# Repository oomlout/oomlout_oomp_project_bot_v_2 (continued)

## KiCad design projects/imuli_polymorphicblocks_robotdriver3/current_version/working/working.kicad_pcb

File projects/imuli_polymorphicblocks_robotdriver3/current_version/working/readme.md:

# polymorphicblocks
 
## summary 
* id: imuli_polymorphicblocks_robotdriver3
* user: imuli
* name: polymorphicblocks
* board: robotdriver3
* repo: https://github.com/imuli/PolymorphicBlocks
* src_file_repo_kicad_pcb: examples/RobotDriver3/RobotDriver3.kicad_pcb
* src_file_repo_kicad_pcb_link: https://github.com/imuli/PolymorphicBlocks/tree/master/examples/RobotDriver3/RobotDriver3.kicad_pcb

* src_file_repo_sch: 
* src_file_repo_sch_link: https://github.com/imuli/PolymorphicBlocks/tree/master/
* full details link: https://github.com/oomlout/oomlout_oomp_project_bot_v_2/tree/main/projects/imuli_polymorphicblocks_robotdriver3/current_version/working

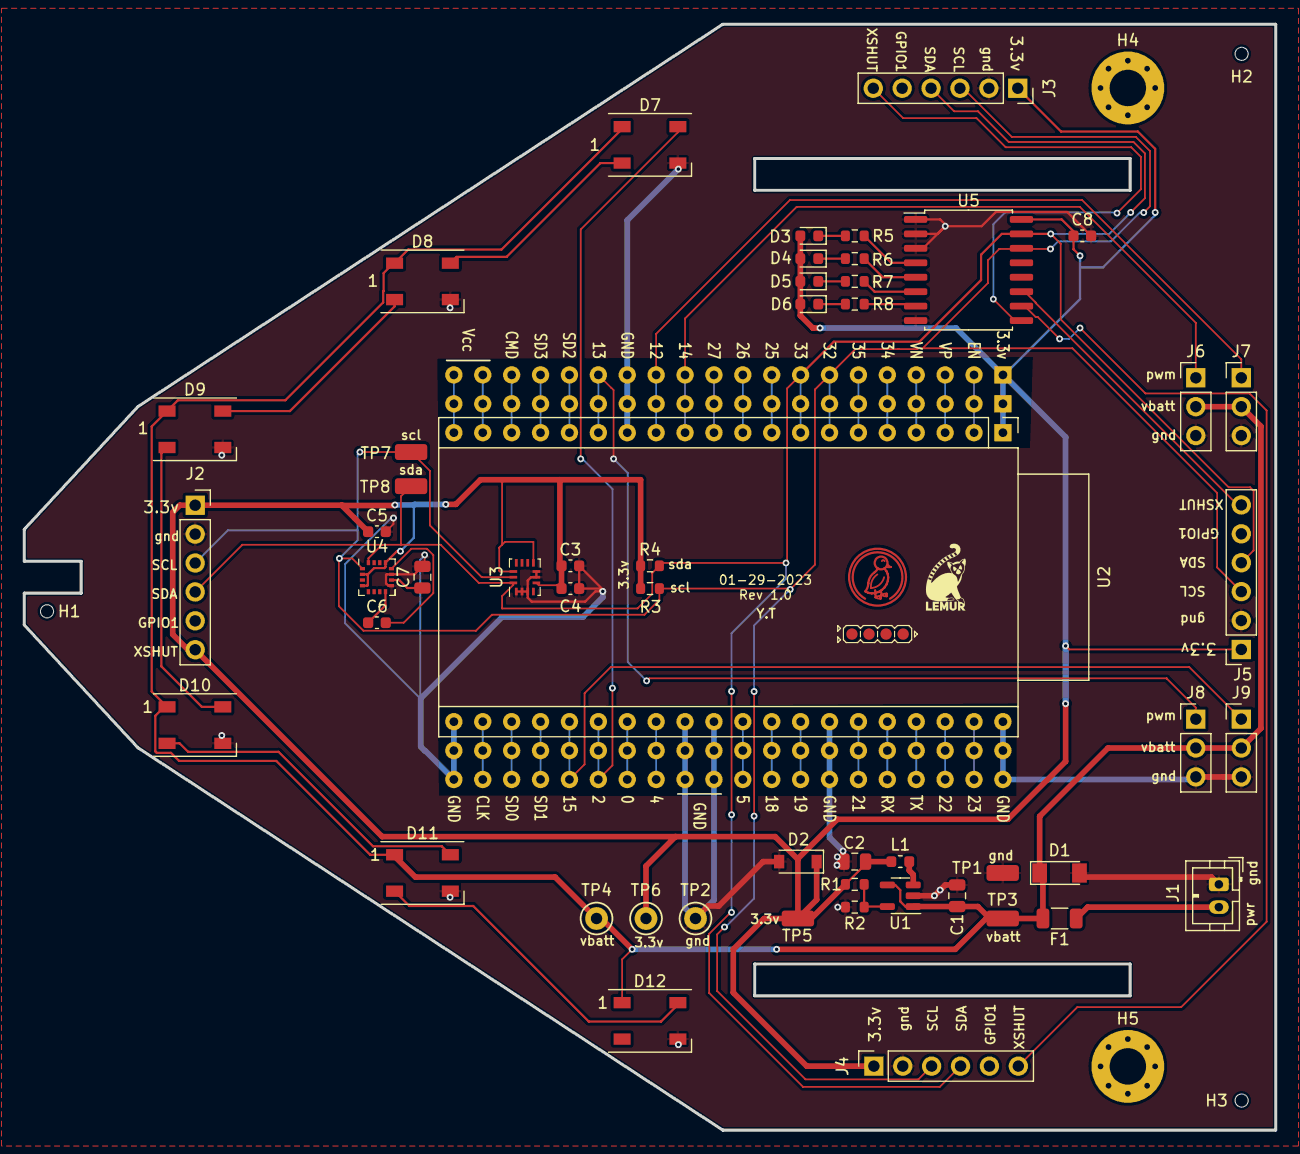
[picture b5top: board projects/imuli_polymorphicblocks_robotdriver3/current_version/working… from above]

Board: 2 copper layers, 110.0 x 97.2 mm, 60 parts (0 on the bottom side), 32 nets.

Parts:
C1, C2, C7: C_0805_2012Metric
C3, C4, C5, C6, C8: C_0603_1608Metric
D1: ZMM5V6-M (ST(Semtech)) - 100nA@1V 25? Single 5.2V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; D_MiniMELF
D2: BZT52C3V6 (SMC(Sangdest Microelectronicstronic (N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; D_SOD-123
D3, D4, D5, D6: KT-0603R (Hubei KENTO Elec) - Red 615~630nm 1.9~2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; LED_0603_1608Metric
D7, D8, D9, D10, D11, D12: WS2812B (Worldsemi); LED_WS2812B_PLCC4_5.0x5.0mm_P3.2mm
F1: MF-NSMF200-2 (BOURNS) - 6V 2A 100A 4A 1206 Resett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; R_1206_3216Metric
H1, H2, H3: JlcToolingHole_1.152mm
H4, H5: M3; MountingHole_3.2mm_M3_Pad_Via
J1: B2B-PH-K (JST); JST_PH_B2B-PH-K_1x02_P2.00mm_Vertical
J2, J3, J4, J5: PinSocket2.54 1x6 (Generic); PinSocket_1x06_P2.54mm_Vertical
J6, J7, J8, J9: PinHeader2.54 1x3 (Generic); PinHeader_1x03_P2.54mm_Vertical
L1: L_0603_1608Metric
R1, R2, R3, R4, R5, R6, R7, R8: R_0603_1608Metric
TP1: 5015 (Keystone) - gnd; TestPoint_TE_RCT_0805
TP2: 5001 (Keystone) - gnd; TestPoint_Keystone_5000-5004_Miniature
TP3: 5015 (Keystone) - vbatt; TestPoint_TE_RCT_0805
TP4: 5001 (Keystone) - vbatt; TestPoint_Keystone_5000-5004_Miniature
TP5: 5015 (Keystone) - v3v3; TestPoint_TE_RCT_0805
TP6: 5001 (Keystone) - v3v3; TestPoint_Keystone_5000-5004_Miniature
TP7: 5015 (Keystone) - i2c_chain_0.scl; TestPoint_TE_RCT_0805
TP8: 5015 (Keystone) - i2c_tp._io_sda_link; TestPoint_TE_RCT_0805
U1: AP3418 (Diodes Incorporated); SOT-23-5
U2: ESP32-WROVER-DEV; ESP32-WROVER-DEV_Chicken
U3: LSM6DS3TR-C (STMicroelectronics); Bosch_LGA-14_3x2.5mm_P0.5mm
U4: QMC5883L (QST); LGA-16_3x3mm_P0.5mm
U5: PCF8574AT (NXP); SOIC-16W_7.5x10.3mm_P1.27mm
U6: Lemur; Symbol_LemurSmall
U7: Duck; Symbol_Duckling
U8: IdDots4; Indicator_IdDots_4

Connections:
batt.pwr: F1.1, J1.2
expander.io.led_0: R5.2, U5.4
expander.io.led_1: R6.2, U5.5
expander.io.led_2: R7.2, U5.6
expander.io.led_3: R8.2, U5.7
expander.io.tof_xshut_1: J3.6, U5.9
expander.io.tof_xshut_2: J4.6, U5.10
expander.io.tof_xshut_3: J5.6, U5.11
gnd: C1.2, C2.2, C3.2, C4.2, C5.2, C7.2, C8.2, D1.2, D2.2, D7.3, D8.3, D9.3, D10.3, D11.3, D12.3, J1.1, J2.2, J3.2, J4.2, J5.2, J6.3, J7.3, J8.3, J9.3, R2.2, TP1.1, TP2.1, U1.2, U2.14, U2.21, U2.29, U2.30, U2.34, U2.40, U3.1, U3.2, U3.3, U3.6, U3.7, U4.9, U4.11, U5.1, U5.2, U5.3, U5.8
i2c_chain_0.scl: J2.3, J3.3, J4.3, J5.3, R3.2, TP7.1, U2.7, U3.13, U4.1, U5.14
i2c_chain_0.sda: J2.4, J3.4, J4.4, J5.4, R4.2, TP8.1, U2.8, U3.14, U4.16, U5.15
leds.led[0].res.a: D3.1, R5.1
leds.led[1].res.a: D4.1, R6.1
leds.led[2].res.a: D5.1, R7.1
leds.led[3].res.a: D6.1, R8.1
mag.c1.pos: C7.1, U4.10
mag.set_cap.neg: C6.2, U4.12
mag.set_cap.pos: C6.1, U4.8
mcu.io2: D7.4, U2.26
reg_3v3.fb.output: R1.2, R2.1, U1.5
reg_3v3.power_path.switch: L1.1, U1.3
servo[0].pwm: J6.1, U2.12
servo[1].pwm: J7.1, U2.13
servo[2].pwm: J8.1, U2.15
servo[3].pwm: J9.1, U2.25
v3v3: C2.1, C3.1, C4.1, C5.1, C8.1, D2.1, D3.2, D4.2, D5.2, D6.2, J2.1, J2.6, J3.1, J4.1, J5.1, L1.2, R1.1, R3.1, R4.1, TP5.1, TP6.1, U2.1, U3.5, U3.8, U3.12, U4.2, U4.4, U4.13, U5.16
vbatt: C1.1, D1.1, D7.1, D8.1, D9.1, D10.1, D11.1, D12.1, F1.2, J6.2, J7.2, J8.2, J9.2, TP3.1, TP4.1, U1.1, U1.4
ws2812bArray.led[0].dout: D7.2, D8.4
ws2812bArray.led[1].dout: D8.2, D9.4
ws2812bArray.led[2].dout: D9.2, D10.4
ws2812bArray.led[3].dout: D10.2, D11.4
ws2812bArray.led[4].dout: D11.2, D12.4

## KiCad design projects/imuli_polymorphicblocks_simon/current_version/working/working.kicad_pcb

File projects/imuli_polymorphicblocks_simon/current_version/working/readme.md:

# polymorphicblocks
 
## summary 
* id: imuli_polymorphicblocks_simon
* user: imuli
* name: polymorphicblocks
* board: simon
* repo: https://github.com/imuli/PolymorphicBlocks
* src_file_repo_kicad_pcb: examples/Simon/Simon.kicad_pcb
* src_file_repo_kicad_pcb_link: https://github.com/imuli/PolymorphicBlocks/tree/master/examples/Simon/Simon.kicad_pcb

* src_file_repo_sch: 
* src_file_repo_sch_link: https://github.com/imuli/PolymorphicBlocks/tree/master/
* full details link: https://github.com/oomlout/oomlout_oomp_project_bot_v_2/tree/main/projects/imuli_polymorphicblocks_simon/current_version/working

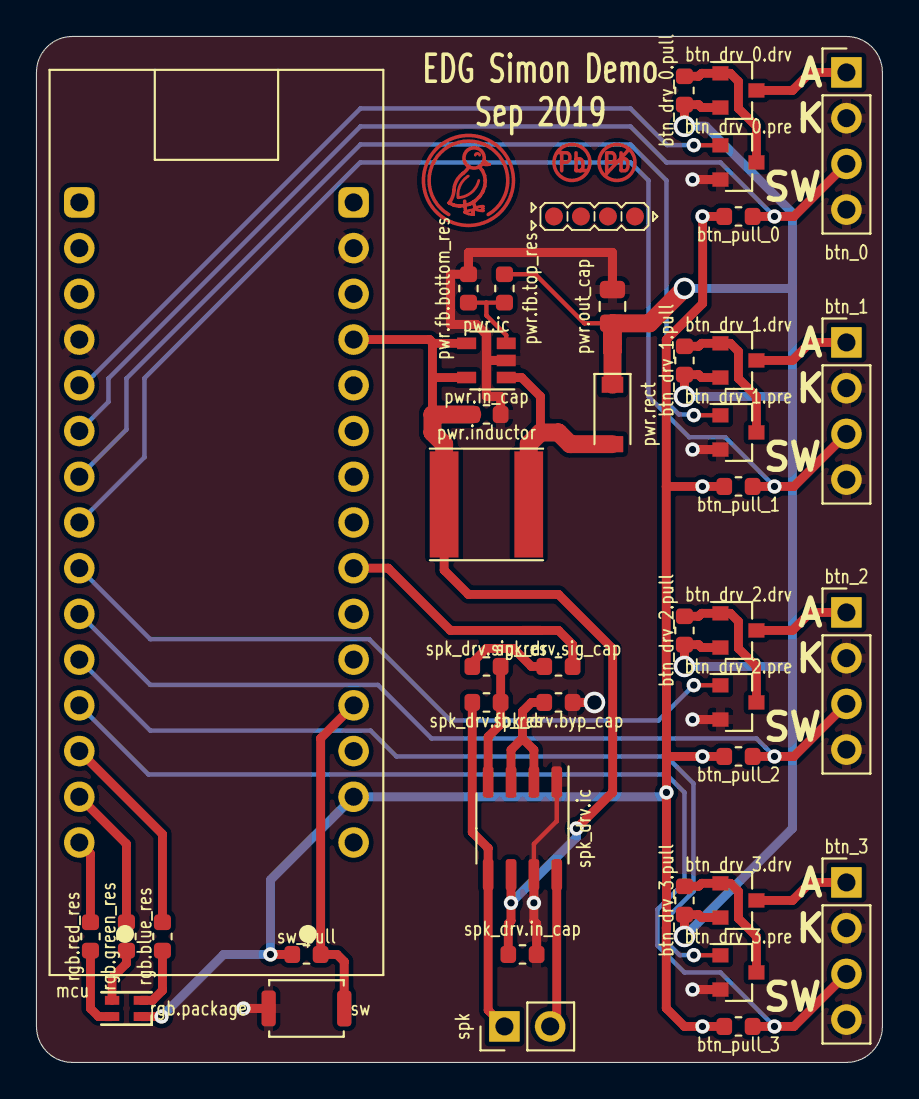
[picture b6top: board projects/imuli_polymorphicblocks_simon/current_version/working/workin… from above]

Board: 2 copper layers, 47.0 x 57.0 mm, 44 parts (0 on the bottom side), 35 nets.

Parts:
btn_0, btn_1, btn_2, btn_3: DomeButton; PinHeader_1x04_P2.54mm_Vertical
btn_drv_0.drv, btn_drv_1.drv, btn_drv_2.drv, btn_drv_3.drv: DMP3099L-7; SOT-23
btn_drv_0.pre, btn_drv_1.pre, btn_drv_2.pre, btn_drv_3.pre: NX138AKR; SOT-23
btn_drv_0.pull, btn_drv_1.pull, btn_drv_2.pull, btn_drv_3.pull: 10000, 1%, 0.1W; R_0603_1608Metric
btn_pull_0, btn_pull_1, btn_pull_2, btn_pull_3: 10000, 1%, 0.1W; R_0603_1608Metric
duck: Duck; Symbol_Duckling
id: IdDots4; Indicator_IdDots_4
leadfree: LeadFree; Indicator_LeadFree
mcu: Nucleo-F303K8; Nucleo32
pwr.fb.bottom_res: 3900, 1%, 0.1W; R_0603_1608Metric
pwr.fb.top_res: 33000, 1%, 0.1W; R_0603_1608Metric
pwr.ic: AP3012; SOT-23-5
pwr.in_cap: 1µF, 10V, CL10A105KP8NNNC; C_0603_1608Metric
pwr.inductor: 68µH, 770mA, NR6028T680M; L_Taiyo-Yuden_NR-60xx
pwr.out_cap: 10µF, 16V, CL21A106KOQNNNG; C_0805_2012Metric
pwr.rect: BAT54GWJ; D_SOD-123
rgb.blue_res, rgb.green_res, rgb.red_res: 1000, 1%, 0.1W; R_0603_1608Metric
rgb.package: LED_RGB_0606
spk: Speaker SP-1504; PinHeader_1x02_P2.54mm_Vertical
spk_drv.byp_cap, spk_drv.in_cap: 1µF, 10V, CL10A105KP8NNNC; C_0603_1608Metric
spk_drv.fb_res, spk_drv.sig_res: 22000, 1%, 0.1W; R_0603_1608Metric
spk_drv.ic: LM4871MX; SO-8_3.9x4.9mm_P1.27mm
spk_drv.sig_cap: 0.47µF, 25V, CL10B474KA8NFNC; C_0603_1608Metric
sw: switch; SW_Push_SPST_NO_Alps_SKRK
sw_pull: 10000, 1%, 0.1W; R_0603_1608Metric

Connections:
btn_1.led_a: btn_1.1, btn_drv_1.drv.3
btn_2.sw1: btn_2.3, btn_pull_2.2, mcu.10
btn_drv_0.control: btn_drv_0.pre.1, mcu.5
btn_drv_0.output: btn_0.1, btn_drv_0.drv.3
btn_drv_0.pre.drain: btn_drv_0.drv.1, btn_drv_0.pre.3, btn_drv_0.pull.2
btn_drv_1.pull.b: btn_drv_1.drv.1, btn_drv_1.pre.3, btn_drv_1.pull.2
btn_drv_2.output: btn_2.1, btn_drv_2.drv.3
btn_drv_2.pre.drain: btn_drv_2.drv.1, btn_drv_2.pre.3, btn_drv_2.pull.2
btn_drv_3.control: btn_drv_3.pre.1, mcu.11
btn_drv_3.drv.gate: btn_drv_3.drv.1, btn_drv_3.pre.3, btn_drv_3.pull.2
btn_drv_3.output: btn_3.1, btn_drv_3.drv.3
gnd: btn_0.2, btn_0.4, btn_1.2, btn_1.4, btn_2.2, btn_2.4, btn_3.2, btn_3.4, btn_drv_0.pre.2, btn_drv_1.pre.2, btn_drv_2.pre.2, btn_drv_3.pre.2, mcu.4, mcu.17, pwr.fb.bottom_res.2, pwr.ic.2, pwr.in_cap.2, pwr.out_cap.2, spk_drv.byp_cap.2, spk_drv.ic.1, spk_drv.ic.7, spk_drv.in_cap.2, sw.1
mcu.dac_1: mcu.24, spk_drv.sig_cap.2
mcu.digital_9: btn_3.3, btn_pull_3.2, mcu.12
mcu.digital_12: btn_drv_2.pre.1, mcu.9
mcu.digital_13: btn_1.3, btn_pull_1.2, mcu.8
mcu.digital_14: btn_drv_1.pre.1, mcu.7
mcu.digital_15: btn_0.3, btn_pull_0.2, mcu.6
mcu.digital_17: mcu.27, sw.2, sw_pull.2
mcu.digital_18: mcu.13, rgb.blue_res.2
mcu.digital_19: mcu.14, rgb.green_res.2
pwr.fb.out: pwr.fb.bottom_res.1, pwr.fb.top_res.2, pwr.ic.3
pwr.sw: pwr.ic.1, pwr.inductor.2, pwr.rect.2
rgb.blue_res.a: rgb.blue_res.1, rgb.package.2
rgb.green_res.a: rgb.green_res.1, rgb.package.3
rgb.red: mcu.15, rgb.red_res.2
rgb.red_res.a: rgb.package.4, rgb.red_res.1
spk_drv.byp_cap.pos: spk_drv.byp_cap.1, spk_drv.ic.2, spk_drv.ic.3
spk_drv.sig_res.a: spk_drv.sig_cap.1, spk_drv.sig_res.1
spk_drv.sig_res.b: spk_drv.fb_res.1, spk_drv.ic.4, spk_drv.sig_res.2
spk_drv.spk1: spk.1, spk_drv.fb_res.2, spk_drv.ic.5
spk_drv.spk2: spk.2, spk_drv.ic.8
v3v3: btn_pull_0.1, btn_pull_1.1, btn_pull_2.1, btn_pull_3.1, mcu.29, rgb.package.1, sw_pull.1
v5: mcu.19, pwr.ic.4, pwr.ic.5, pwr.in_cap.1, pwr.inductor.1, spk_drv.ic.6, spk_drv.in_cap.1
v12: btn_drv_0.drv.2, btn_drv_0.pull.1, btn_drv_1.drv.2, btn_drv_1.pull.1, btn_drv_2.drv.2, btn_drv_2.pull.1, btn_drv_3.drv.2, btn_drv_3.pull.1, pwr.fb.top_res.1, pwr.out_cap.1, pwr.rect.1

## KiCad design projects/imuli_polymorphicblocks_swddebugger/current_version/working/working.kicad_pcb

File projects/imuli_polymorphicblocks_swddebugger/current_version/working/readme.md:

# polymorphicblocks
 
## summary 
* id: imuli_polymorphicblocks_swddebugger
* user: imuli
* name: polymorphicblocks
* board: swddebugger
* repo: https://github.com/imuli/PolymorphicBlocks
* src_file_repo_kicad_pcb: examples/SwdDebugger/SwdDebugger.kicad_pcb
* src_file_repo_kicad_pcb_link: https://github.com/imuli/PolymorphicBlocks/tree/master/examples/SwdDebugger/SwdDebugger.kicad_pcb

* src_file_repo_sch: 
* src_file_repo_sch_link: https://github.com/imuli/PolymorphicBlocks/tree/master/
* full details link: https://github.com/oomlout/oomlout_oomp_project_bot_v_2/tree/main/projects/imuli_polymorphicblocks_swddebugger/current_version/working

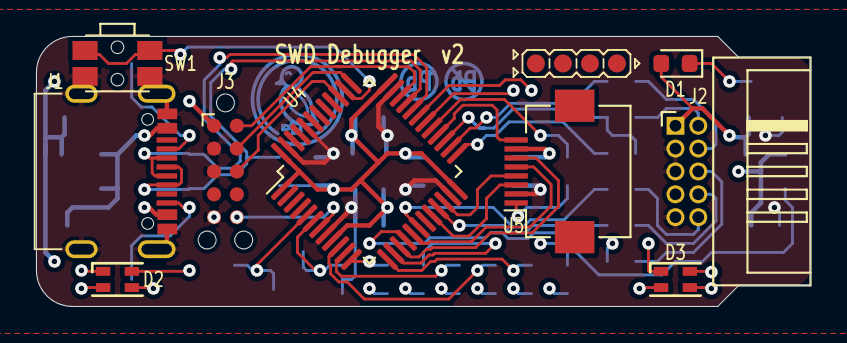
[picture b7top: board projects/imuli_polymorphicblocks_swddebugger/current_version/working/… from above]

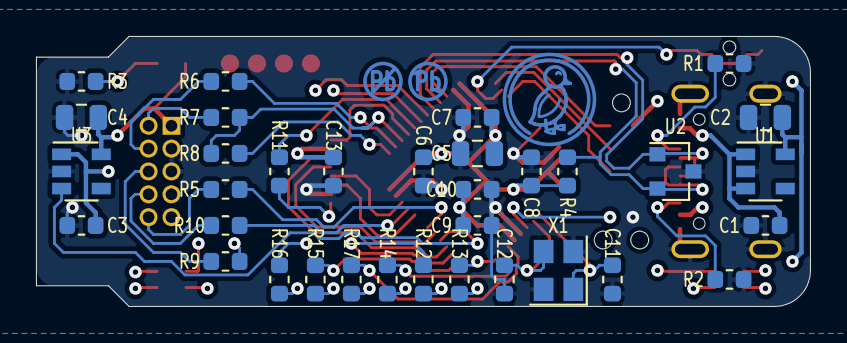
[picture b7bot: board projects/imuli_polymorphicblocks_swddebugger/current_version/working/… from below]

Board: 4 copper layers, 43.0 x 15.0 mm, 46 parts (36 on the bottom side), 47 nets.

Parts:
1: LeadFree; Indicator_LeadFree
2: IdDots4; Indicator_IdDots_4
C1, C3, C10, C13: CL10A105KP8NNNC (Samsung Electro-Mechanics) - 1µF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; C_0603_1608Metric
C2, C4: CL21B225KPFNNNE (Samsung Electro-Mechanics) - 2.2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; C_0805_2012Metric
C5: CL21A475KQFNNNG (Samsung Electro-Mechanics) - 4.7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; C_0805_2012Metric
C6, C7, C8: CL10B104KB8NNNC (Samsung Electro-Mechanics) - 0.1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; C_0603_1608Metric
C9: CL10B103KB8NNNC (Samsung Electro-Mechanics) - 100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; C_0603_1608Metric
C11, C12: CC0603GRNPO9BN180 (Yageo) - 18pF, 50V; C_0603_1608Metric
D1: LED; LED_0603_1608Metric
D2, D3: EAST1616RGBB2 (Everlight Electronics Co Ltd); LED_RGB_0606
J1: COM-15111 (Sparkfun); USB_C_Receptacle_BSC_A40-00119
J2: 3220-10-0200-00 (CNC Tech) - SWD; PinHeader_2x05_P1.27mm_Horizontal_Shrouded
J3: SWD; Tag-Connect_TC2050-IDC-NL_2x05_P1.27mm_Vertical
R1, R2: 5.1k, 1%, 0.1W; R_0603_1608Metric
R3, R12, R13, R14, R15, R16, R17: 1k, 1%, 0.1W; R_0603_1608Metric
R4: 1.5k, 1%, 0.1W; R_0603_1608Metric
R5, R6, R7, R9, R10: 22, 1%, 0.1W; R_0603_1608Metric
R8, R11: 100, 1%, 0.1W; R_0603_1608Metric
SW1: EVQ-P7C01P; SW_SPST_EVQP7C
U1, U3: AP2204K-3.3 (Diodes Incorporated); SOT-23-5
U2: TPD2E009 (Texas Instruments); SOT-23
U4: STM32F103xxT6 (STMicroelectronics); LQFP-48_7x7mm_P0.5mm
U5: QT096T_IF09, FH12-8S-0.5SH(55); Hirose_FH12-8S-0.5SH_1x08-1MP_P0.50mm_Horizontal
U6: Duck; Symbol_Duckling
X1: 7V-12.000MAHE-T (TXC); Oscillator_SMD_Abracon_ASE-4Pin_3.2x2.5mm

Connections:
(adapter)tdi_res.a.dst: R10.1, U4.21
crystal.crystal.b: C12.1, U4.6, X1.3
gnd: C1.2, C2.2, C3.2, C4.2, C5.2, C6.2, C7.2, C8.2, C9.2, C10.2, C11.2, C12.2, C13.2, J1.A1B12, J1.B1A12, J1.S, J2.3, J2.5, J2.9, J3.2, J3.3, J3.5, R1.1, R2.1, R3.2, SW1.1, U1.2, U2.3, U3.2, U4.8, U4.23, U4.35, U4.44, U4.47, U5.2, X1.2, X1.4
lcd.cs: U4.28, U5.8
lcd.device.leda: R11.2, U5.1
lcd.reset: U4.20, U5.3
lcd.rs: U4.22, U5.4
lcd.spi.sck: U4.15, U5.6
led_target.package.k: D1.1, R3.1
led_target.signal: C4.1, D1.2, J2.1, U3.5
mcu.digital_12: SW1.2, U4.38
mcu.digital_13: R17.2, U4.10
mcu.digital_15: R15.2, U4.13
mcu.digital_18: R12.2, U4.14
mcu.digital_22: R11.1, U4.29
mcu.digital_26: R8.1, U4.25
mcu.digital_27: R7.1, R8.2, U4.27
mcu.digital_28: R6.1, U4.26
mcu.spi_0.mosi: U4.17, U5.5
mcu.swd.swdio: J3.10, U4.34
mcu.swd.swo: J3.8, U4.39
mcu.xtal.xtal_in: C11.1, U4.5, X1.1
rgb_tgt.blue_res.a: D3.2, R17.1
rgb_tgt.green: R16.2, U4.30
rgb_tgt.green_res.a: D3.3, R16.1
rgb_tgt.package.red_k: D3.4, R15.1
rgb_usb.blue: R14.2, U4.11
rgb_usb.blue_res.a: D2.2, R14.1
rgb_usb.green: R13.2, U4.12
rgb_usb.green_res.a: D2.3, R13.1
rgb_usb.red_res.a: D2.4, R12.1
swd.swd.reset: J3.6, U4.7
swd.swd.swclk: J3.9, U4.37
target.swd.reset: J2.10, R5.2
target.swd.swdio: J2.2, R7.2
target_drv.reset_in: R5.1, U4.18
target_drv.swd.swclk: J2.4, R6.2
target_drv.swd.swo: J2.6, R9.2
target_drv.swo_out: R9.1, U4.31
target_reg.en: U3.3, U4.16
tdi_res.b: J2.8, R10.2
usb.port.A5: J1.A5, R1.2
usb.port.B5: J1.B5, R2.2
usb_net.d_N: J1.A7, J1.B7, U2.1, U4.32
usb_net.d_P: J1.A6, J1.B6, R4.2, U2.2, U4.33
v3v3: C2.1, C5.1, C6.1, C7.1, C8.1, C9.1, C10.1, C13.1, D2.1, D3.1, J3.1, R4.1, U1.5, U4.1, U4.9, U4.24, U4.36, U4.48, U5.7
vusb: C1.1, C3.1, J1.A4B9, J1.B4A9, U1.1, U1.3, U3.1

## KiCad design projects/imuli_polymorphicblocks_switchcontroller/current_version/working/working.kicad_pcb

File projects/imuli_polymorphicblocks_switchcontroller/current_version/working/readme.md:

# polymorphicblocks
 
## summary 
* id: imuli_polymorphicblocks_switchcontroller
* user: imuli
* name: polymorphicblocks
* board: switchcontroller
* repo: https://github.com/imuli/PolymorphicBlocks
* src_file_repo_kicad_pcb: examples/SwitchController/SwitchController.kicad_pcb
* src_file_repo_kicad_pcb_link: https://github.com/imuli/PolymorphicBlocks/tree/master/examples/SwitchController/SwitchController.kicad_pcb

* src_file_repo_sch: 
* src_file_repo_sch_link: https://github.com/imuli/PolymorphicBlocks/tree/master/
* full details link: https://github.com/oomlout/oomlout_oomp_project_bot_v_2/tree/main/projects/imuli_polymorphicblocks_switchcontroller/current_version/working

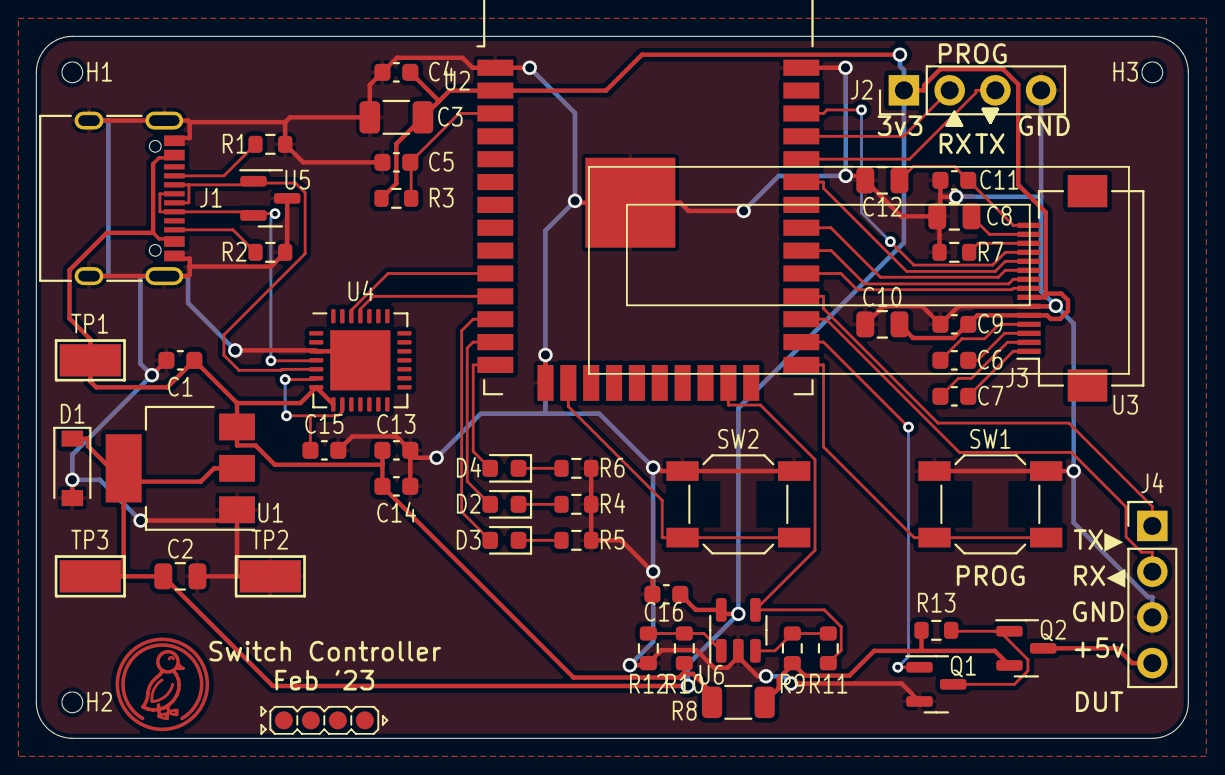
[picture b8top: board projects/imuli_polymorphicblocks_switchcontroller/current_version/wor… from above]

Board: 2 copper layers, 64.0 x 39.0 mm, 55 parts (0 on the bottom side), 42 nets.

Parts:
C1, C4, C5, C6, C7, C9, C11, C13, C14, C15, C16: C_0603_1608Metric
C2, C8, C10, C12: C_0805_2012Metric
C3: C_1206_3216Metric
D1: BZT52C3V6 (SMC(Sangdest Microelectronicstronic (N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; D_SOD-123
D2: KT-0603R (Hubei KENTO Elec) - Red 615~630nm 1.9~2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; LED_0603_1608Metric
D3, D4: LED_0603_1608Metric
H1, H2, H3: JlcToolingHole_1.152mm
J1: COM-15111 (Sparkfun); USB_C_Receptacle_XKB_U262-16XN-4BVC11
J2, J4: PinHeader2.54 1x4 (Generic); PinHeader_1x04_P2.54mm_Vertical
J3: AFC01-S15FCA-00 (Jushuo); Hirose_FH12-15S-0.5SH_1x15-1MP_P0.50mm_Horizontal
Q1: 2N7002 (Changjiang Electronics Tech (CJ)) - 60V 1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; SOT-23
Q2: AO3401A (Alpha & Omega Semicon) - 30V 4A 44m?@10V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; SOT-23
R1, R2, R3, R4, R5, R6, R7, R9, R10, R11, R12, R13: R_0603_1608Metric
R8: R_1206_3216Metric
SW1, SW2: 5.1mm switch; SW_SPST_SKQG_WithoutStem
TP1: 5015 (Keystone) - vusb; TestPoint_Keystone_5015_Micro-Minature
TP2: 5015 (Keystone) - gnd; TestPoint_Keystone_5015_Micro-Minature
TP3: 5015 (Keystone) - v3v3; TestPoint_Keystone_5015_Micro-Minature
U1: LD1117S33TR (STMicroelectronics); SOT-223-3_TabPin2
U2: ESP32-WROOM-32 (Espressif Systems); ESP32-WROOM-32
U3: ER-OLED-0.91-e (EastRising); Lcd_Er_Oled0.91_3_Outline
U4: CP2102 (Silicon Labs); QFN-28-1EP_5x5mm_P0.5mm_EP3.35x3.35mm
U5: PESD5V0X1BT (Nexperia); SOT-23
U6: LMV321 (Texas Instruments); SOT-23-5
U7: Duck; Symbol_Duckling
U8: IdDots4; Indicator_IdDots_4

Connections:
conn.uart.rx: J4.1, U2.28
conn.uart.tx: J4.2, U2.27
gnd: C1.2, C2.2, C3.2, C4.2, C5.2, C8.2, C9.2, C10.2, C11.2, C12.2, C13.2, C14.2, C15.2, C16.2, D1.2, J1.A1, J1.A12, J1.B1, J1.B12, J1.S1, J2.4, J3.6, J4.3, Q1.2, R1.1, R2.1, R4.2, R5.2, R6.2, R7.2, R12.1, SW1.1, SW2.1, TP2.1, U1.1, U2.1, U2.15, U2.38, U2.39, U4.3, U4.29, U5.3, U6.2
isense.amp.r1.b: R9.2, R11.2, U6.3
isense.amp.r2.b: R10.2, R12.2, U6.1
isense.out: R11.1, U2.23, U6.4
isense.pwr_out: Q2.2, R8.2, R9.1, R13.1
lcd.c1_cap.neg: C6.2, J3.4
lcd.c1_cap.pos: C6.1, J3.3
lcd.c2_cap.neg: C7.2, J3.2
lcd.c2_cap.pos: C7.1, J3.1
lcd.cs: J3.8, U2.29
lcd.dc: J3.10, U2.31
lcd.device.vcc: C11.1, C12.1, J3.15
lcd.device.vcomh: C8.1, J3.14
lcd.iref_res.a: J3.13, R7.1
lcd.reset: J3.9, U2.30
lcd.spi.mosi: J3.12, U2.36
lcd.spi.sck: J3.11, U2.33
ledb.res.a: D4.1, R6.1
ledb.signal: D4.2, U2.14
ledg.res.a: D3.1, R5.1
ledg.signal: D3.2, U2.12
ledr.res.a: D2.1, R4.1
ledr.signal: D2.2, U2.13
mcu.ic.chip_pu: C5.1, R3.2, U2.3
mcu.prog.out: SW1.2, U2.25
mcu.uart0.uart.rx: J2.2, U2.35
mcu.uart0.uart.tx: J2.3, U2.34
sw1.out: SW2.2, U2.16
sw.control: Q1.1, U2.26
sw.output: J4.4, Q2.3
sw.pre.drain: Q1.3, Q2.1, R13.2
usb.conn.A5: J1.A5, R1.2
usb.conn.B5: J1.B5, R2.2
usb.usb.dm: J1.A7, J1.B7, U4.5, U5.1
usb.usb.dp: J1.A6, J1.B6, U4.4, U5.2
usb_uart.ic.vdd: C15.1, U4.6, U4.9
usb_uart.uart.rx: U2.11, U4.25
usb_uart.uart.tx: U2.10, U4.26
v3v3: C2.1, C3.1, C4.1, C9.1, C10.1, C16.1, D1.1, J2.1, J3.5, J3.7, R3.1, TP3.1, U1.2, U2.2, U6.5
vusb: C1.1, C13.1, C14.1, J1.A4, J1.A9, J1.B4, J1.B9, R8.1, R10.1, TP1.1, U1.3, U4.7, U4.8
